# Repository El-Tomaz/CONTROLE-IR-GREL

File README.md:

# CONTROLE IR GREL

Projeto de controle remoto infravermelho (IR) desenvolvido para o laboratório do Grupo de Robótica Educacional Livre (GREL), do IFPB.
O controle é baseado na ESP01. A escolha deste módulo se deu pela necessidade de poucas GPIO's (1 para os LED's IR e 3 para os botões) e custo e tamanho reduzidos.

Projeto utiliza como base a biblioteca: (IR)[]

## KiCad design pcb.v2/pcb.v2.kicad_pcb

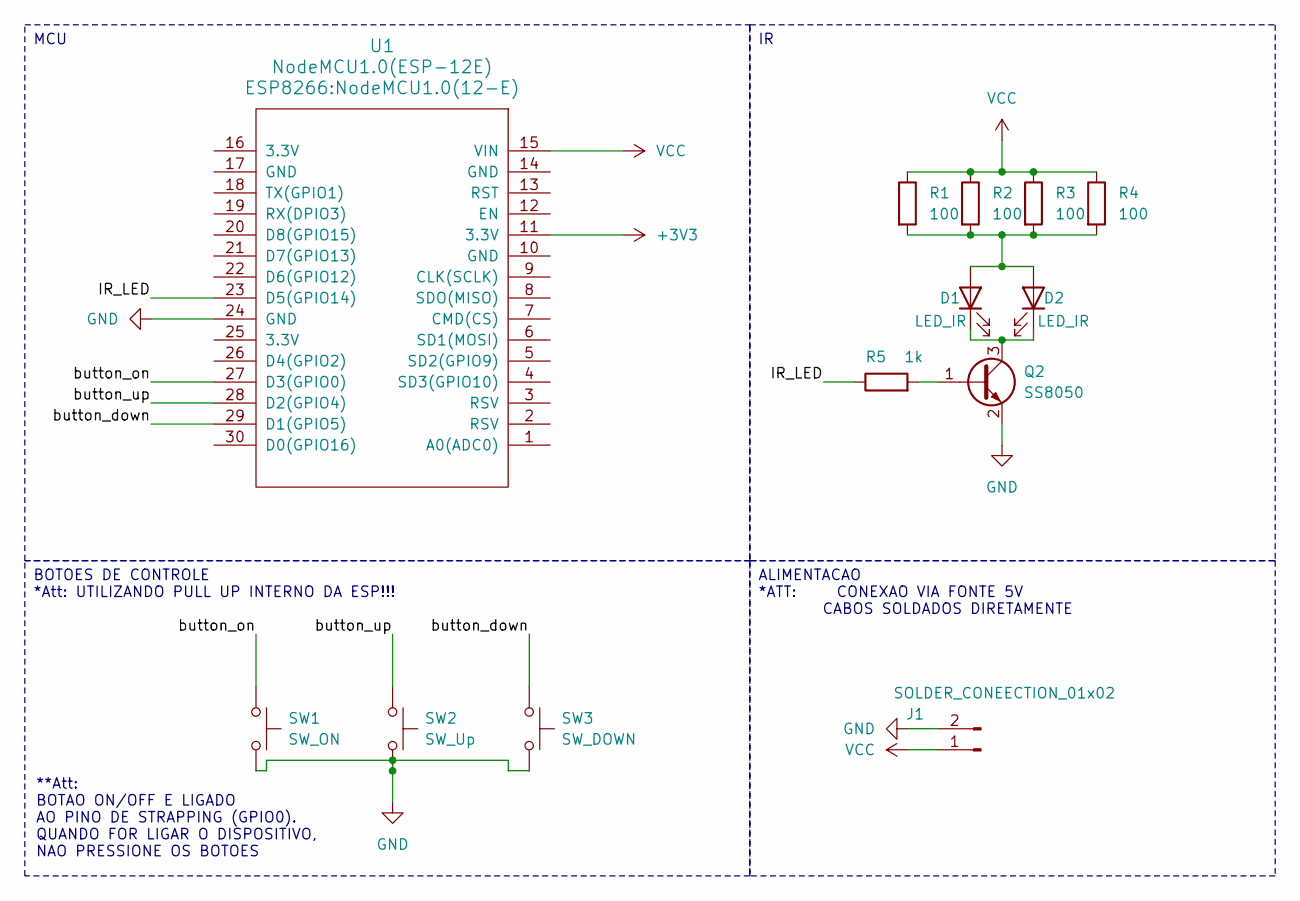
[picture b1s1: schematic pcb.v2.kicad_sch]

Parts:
D1, D2: LED_IR; LED_D5.0mm_Horizontal_O3.81mm_Z9.0mm
J1: SOLDER_CONEECTION_01x02
Q2: SS8050; SOT-23
R1, R2, R3, R4: 100; R_0805_2012Metric_Pad1.20x1.40mm_HandSolder
R5: 1k; R_0805_2012Metric_Pad1.20x1.40mm_HandSolder
SW1: SW_ON; my_push_button
SW2: SW_Up; my_push_button
SW3: SW_DOWN; my_push_button
U1: NodeMCU1.0(ESP-12E); NodeMCU1.0(12-E)

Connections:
+3V3: U1.11 (3.3V)
/IR_LED: R5.1, U1.23 (D5(GPIO14))
/button_down: SW3.1, U1.29 (D1(GPIO5))
/button_on: SW1.1, U1.27 (D3(GPIO0))
/button_up: SW2.1, U1.28 (D2(GPIO4))
GND: J1.2, Q2.2 (E), SW1.2, SW2.2, SW3.2, U1.24 (GND)
unnamed: D1.2 (A), D2.2 (A), R1.2, R2.2, R3.2, R4.2
unnamed: D1.1 (K), D2.1 (K), Q2.3 (C)
unnamed: Q2.1 (B), R5.2
VCC: J1.1, R1.1, R2.1, R3.1, R4.1, U1.15 (VIN)

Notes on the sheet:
**Att: BOTAO ON/OFF E LIGADO AO PINO DE STRAPPING (GPIO0). QUANDO FOR LIGAR O DISPOSITIVO, NAO PRESSIONE OS BOTOES
MCU
ALIMENTACAO *ATT: CONEXAO VIA FONTE 5V CABOS SOLDADOS DIRETAMENTE
BOTOES DE CONTROLE *Att: UTILIZANDO PULL UP INTERNO DA ESP!!!

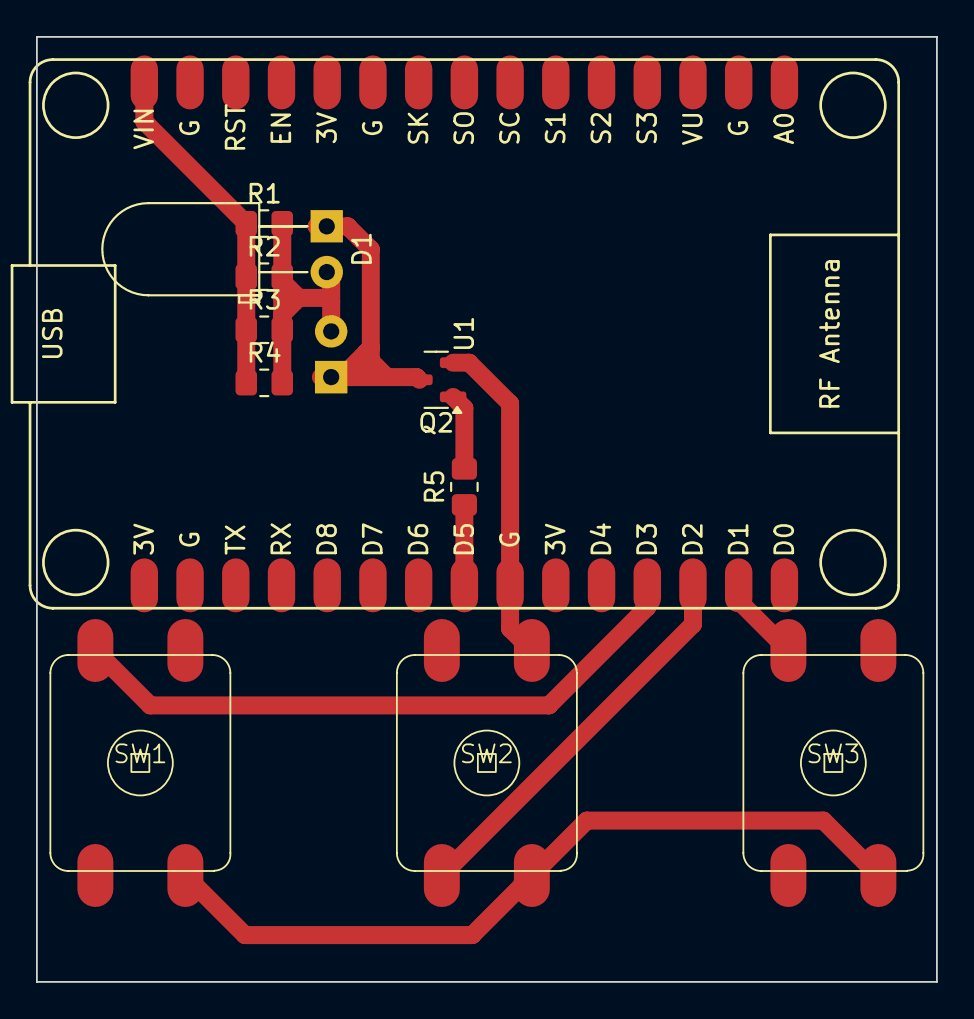
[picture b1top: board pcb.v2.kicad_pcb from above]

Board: 2 copper layers, 50.0 x 52.5 mm, 12 parts (1 on the bottom side), 9 nets.

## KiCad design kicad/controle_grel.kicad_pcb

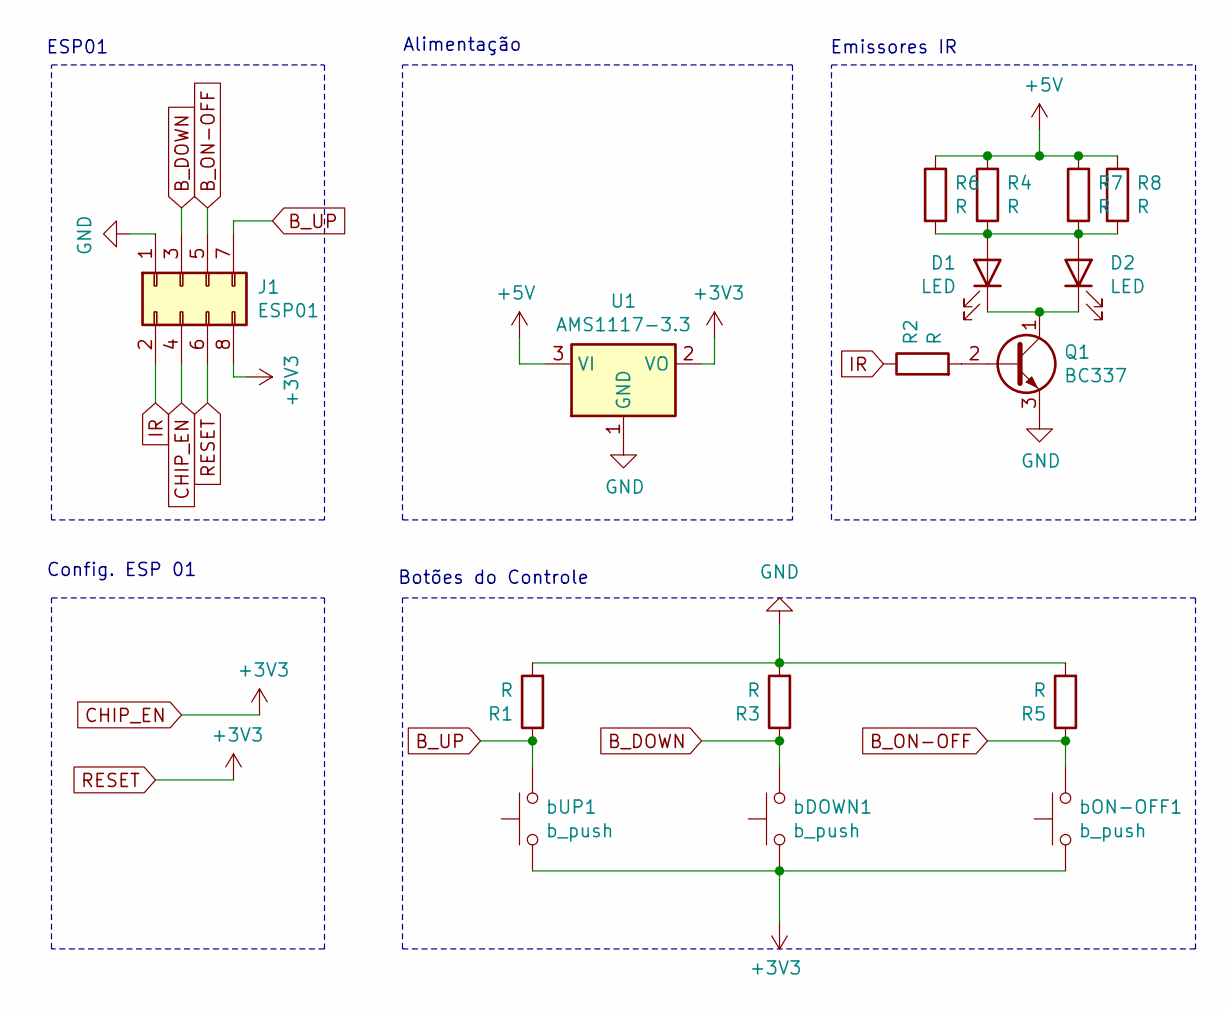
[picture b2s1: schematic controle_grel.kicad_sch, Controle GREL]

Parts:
D1, D2: LED; LED_D5.0mm
J1: ESP01; PinSocket_2x04_P2.54mm_Vertical_SMD
Q1: BC337; PinHeader_1x03_P2.54mm_Horizontal
R1, R2, R3, R4, R5, R6, R7, R8: R; R_1206_3216Metric
U1: AMS1117-3.3; SOT-223-3_TabPin2
bDOWN1: b_push; PinHeader_1x02_P2.54mm_Vertical
bON-OFF1: b_push; PinHeader_1x02_P2.54mm_Vertical
bUP1: b_push; PinHeader_1x02_P2.54mm_Vertical

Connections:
+5V: R4.1, R6.1, R7.1, R8.1, U1.3 (VI)
B_DOWN: J1.3, R3.1, bDOWN1.2
B_ON-OFF: J1.5, R5.1, bON-OFF1.2
B_UP: J1.7, R1.1, bUP1.2
CHIP_EN: J1.4, J1.6, J1.8, U1.2 (VO), bDOWN1.1, bON-OFF1.1, bUP1.1
GND: J1.1, Q1.3 (E), R1.2, R3.2, R5.2, U1.1 (GND)
IR: J1.2, R2.1
unnamed: D1.2 (A), D2.2 (A), R4.2, R6.2, R7.2, R8.2
unnamed: D1.1 (K), D2.1 (K), Q1.1 (C)
unnamed: Q1.2 (B), R2.2

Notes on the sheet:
Botões do Controle
Config. ESP 01
Emissores IR
ESP01
Alimentação

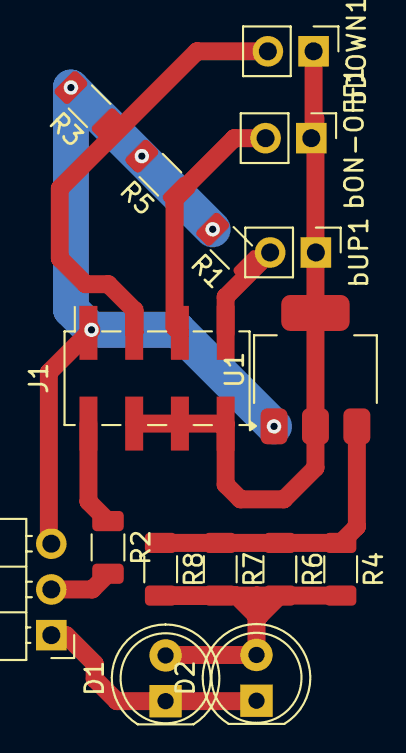
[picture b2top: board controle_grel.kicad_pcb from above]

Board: 2 copper layers, 16 parts (0 on the bottom side), 10 nets.

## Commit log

2025-06-24 Adicionado arquivo kicad!!!
2025-06-24 pcb: corrijindo pinagem esp01 e aumentando espaçamento
2025-06-24 firmware: adicionado primeiro sketch de teste
    docs: add reame!
2025-07-01 pcb: corrigido lado do ams1117 (colocando no botton)
2025-07-30 Consegui corroer a plaquinhaaaa
2025-09-05 Adicionando Blynk, amanha testo direitinho!
2025-09-14 dev: mqtt funfando! dev: wifi maneger implementado! sem precisar codar as credenciais mais
    todo: remover tokens (nao sei como ainda)
    todo: implementar botoes
2025-09-14 dev: botoes implementados, uplink para blynk mqtt implementado
    todo: downlink do blynk mqtt (o controle local terá prioridade)
    todo: pcb
    todo: case 3d
2025-09-14 dev: downlink implementado, a esp consegue atualizar blynk e puxar dados de la tbm
2025-09-15 pcb: criada pcb com nodemcu todo: modelo da case no freecad todo: pcb apenas com modulo 12E
    note: testando transistores sot23 (acredito que dao conta da potencia do disparo IR)
